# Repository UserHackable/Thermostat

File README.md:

## Thermostat 

### Board dimensions

* (194952, 194961) original units
* (1.9495, 1.9496) inches
* (49.5178, 49.5201) mm

| Front | Back |
| --- | --- |
|  |  |

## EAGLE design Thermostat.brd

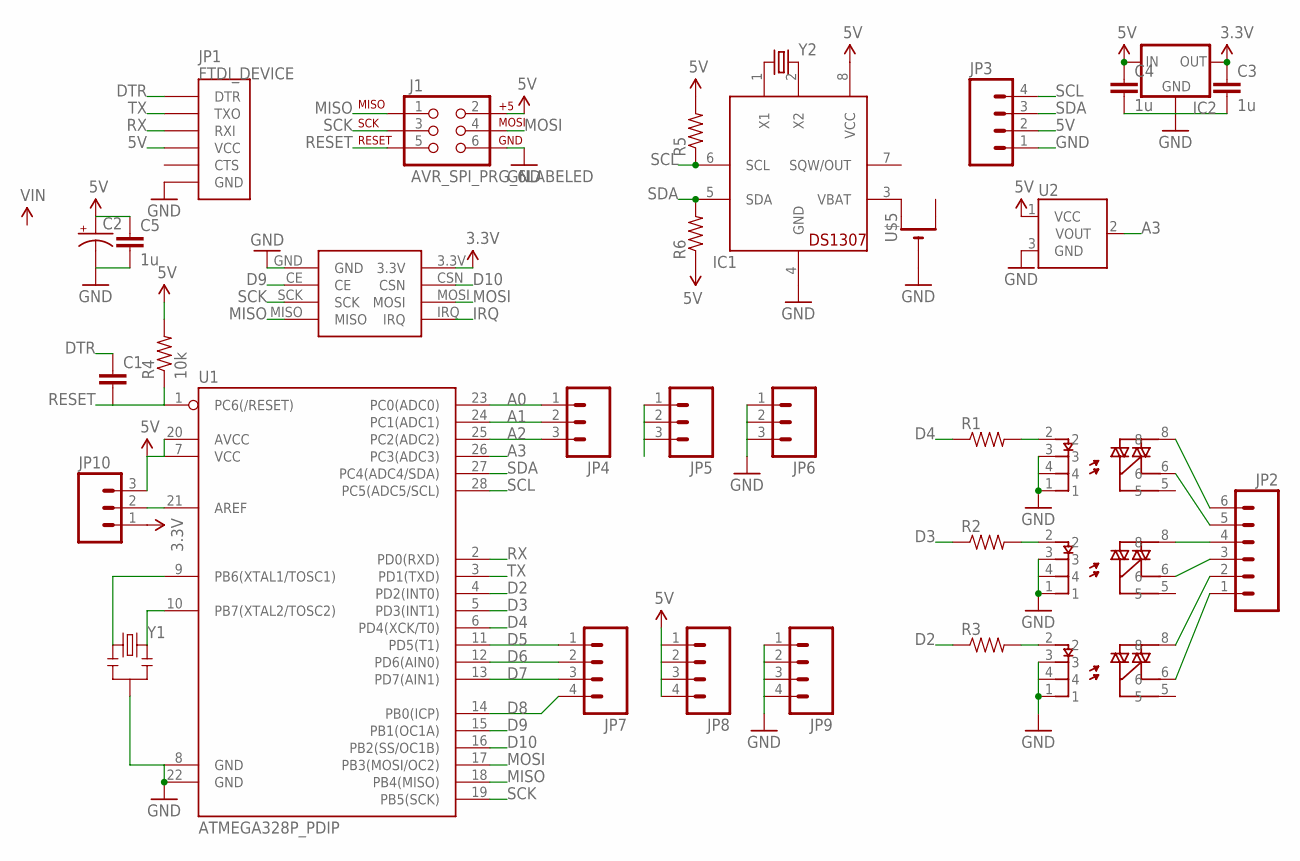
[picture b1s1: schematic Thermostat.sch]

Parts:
C1: CAPPTH; CAP-PTH-SMALL
C2: CAP_POLPTH1; CPOL-RADIAL-100UF-25V
C3, C4, C5: 1u; CAP-PTH-SMALL
IC1: DS1307; DIL08
IC2: MCP1700INLINE; TO92-INLINE
J1: AVR_SPI_PRG_6LABELED; 2X3-NS
JP1: FTDI_DEVICE; FTDI_DEVICE_SIDE
JP2: M063.5MM-6; SCREWTERMINAL-3.5MM-6
JP3, JP7, JP8, JP9: M04PTH; 1X04
JP4, JP5, JP6, JP10: M03PTH; 1X03
R1, R2, R3, R5, R6: RESISTORAXIAL-0.3; AXIAL-0.3
R4: 10k; AXIAL-0.3
U1: ATMEGA328P_PDIP; DIL28-3
U2: TMP36GT9; TO-92
U$1, U$2, U$3: PR39MF5; PR39MF51
U$4: RF24_MODULE; RF24_SOCKET
U$5: CR1220THM; CR1220-THM
Y1: RESONATORPTH; RESONATOR-PTH
Y2: CRYSTALTC26H; TC26H

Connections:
3.3V: C3.1, IC2.3 (OUT), JP10.1, U$4.3.3V
5V: C2.1 (+), C4.1, C5.1, IC1.8 (VCC), IC2.2 (IN), J1.2, JP1.P$4 (VCC), JP3.2, JP8.1, JP8.2, JP8.3, JP8.4, JP10.3, R4.P$2 (2), R5.P$2 (2), R6.P$1 (1), U1.7 (VCC), U1.20 (AVCC), U2.1 (VCC)
A0: JP4.1, U1.23 (PC0(ADC0))
A1: JP4.2, U1.24 (PC1(ADC1))
A2: JP4.3, U1.25 (PC2(ADC2))
A3: U1.26 (PC3(ADC3)), U2.2 (VOUT)
AREF: JP5.1, JP5.2, JP5.3, JP10.2, U1.21 (AREF)
D2: R3.P$1 (1), U1.4 (PD2(INT0))
D3: R2.P$1 (1), U1.5 (PD3(INT1))
D4: R1.P$1 (1), U1.6 (PD4(XCK/T0))
D5: JP7.1, U1.11 (PD5(T1))
D6: JP7.2, U1.12 (PD6(AIN0))
D7: JP7.3, U1.13 (PD7(AIN1))
D8: JP7.4, U1.14 (PB0(ICP))
D9: U1.15 (PB1(OC1A)), U$4.CE
D10: U1.16 (PB2(SS/OC1B)), U$4.CSN
DTR: C1.1, JP1.P$1 (DTR)
GND: C2.2 (-), C3.2, C4.2, C5.2, IC1.4 (GND), IC2.1 (GND), J1.6, JP1.P$6 (GND), JP3.1, JP6.1, JP6.2, JP6.3, JP9.1, JP9.2, JP9.3, JP9.4, U1.8 (GND), U1.22 (GND), U2.3 (GND), U$1.1, U$1.3, U$1.4, U$2.1, U$2.3, U$2.4, U$3.1, U$3.3, U$3.4, U$4.GND, U$5.-, Y1.2
IRQ: U$4.IRQ
MISO: J1.1, U1.18 (PB4(MISO)), U$4.MISO
MOSI: J1.4, U1.17 (PB3(MOSI/OC2)), U$4.MOSI
unnamed: JP2.6, U$1.8
unnamed: R1.P$2 (2), U$1.2
unnamed: JP2.5, U$1.6
unnamed: JP2.4, U$2.8
unnamed: JP2.3, U$2.6
unnamed: JP2.2, U$3.8
unnamed: R2.P$2 (2), U$2.2
unnamed: JP2.1, U$3.6
unnamed: IC1.2 (X2), Y2.2
unnamed: R3.P$2 (2), U$3.2
unnamed: IC1.1 (X1), Y2.1
unnamed: IC1.3 (VBAT), U$5.+1 (+)
unnamed: U1.9 (PB6(XTAL1/TOSC1)), Y1.1
unnamed: U1.10 (PB7(XTAL2/TOSC2)), Y1.3
RESET: C1.2, J1.5, R4.P$1 (1), U1.1 (PC6(/RESET))
RX: JP1.P$3 (RXI), U1.2 (PD0(RXD))
SCK: J1.3, U1.19 (PB5(SCK)), U$4.SCK
SCL: IC1.6 (SCL), JP3.4, R5.P$1 (1), U1.28 (PC5(ADC5/SCL))
SDA: IC1.5 (SDA), JP3.3, R6.P$2 (2), U1.27 (PC4(ADC4/SDA))
TX: JP1.P$2 (TXO), U1.3 (PD1(TXD))

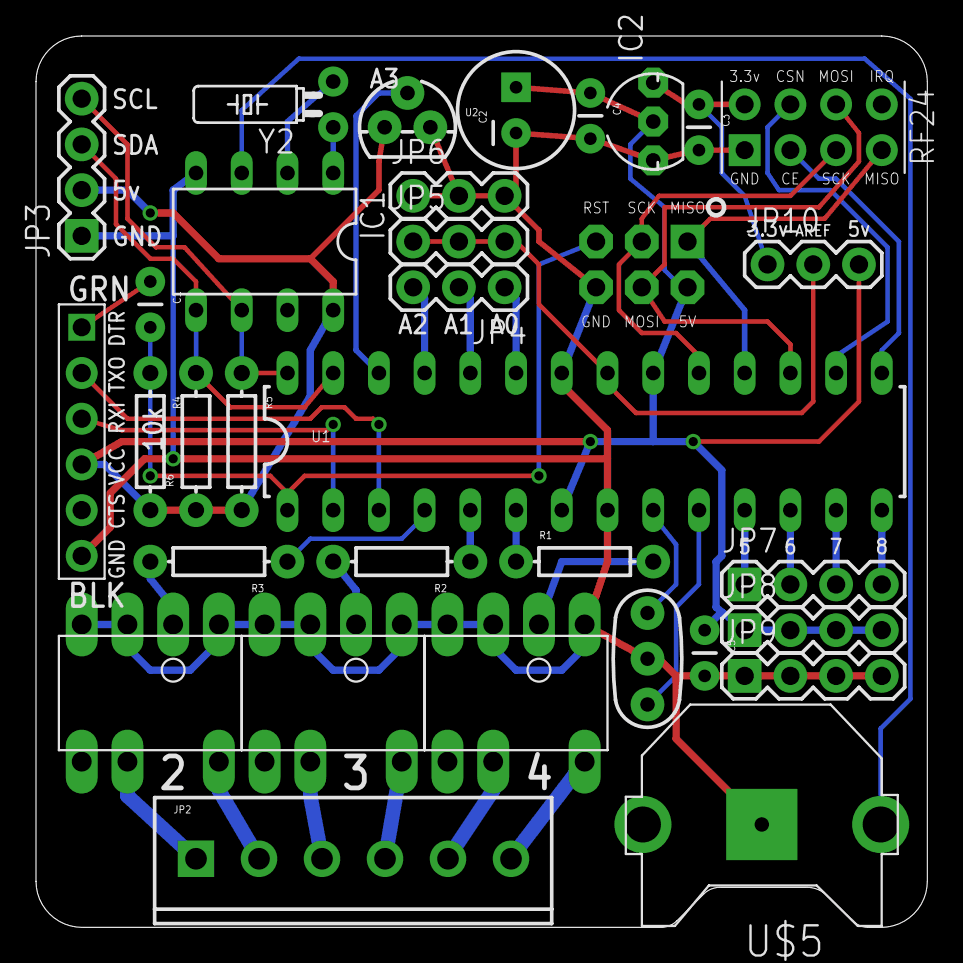
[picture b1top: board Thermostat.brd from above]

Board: 2 copper layers, 49.5 x 49.5 mm, 33 parts (0 on the bottom side), 40 nets.

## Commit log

2016-04-08 from Makefile

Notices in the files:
parts and their libraries:
SparkFun-Resistors: Licensing: Creative Commons ShareAlike 4.0 International - https://creativecommons.org/licenses/by-sa/4.0
